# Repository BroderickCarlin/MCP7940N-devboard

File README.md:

# MCP7940N-devboard
A basic devboard for the MCP7940N RTC

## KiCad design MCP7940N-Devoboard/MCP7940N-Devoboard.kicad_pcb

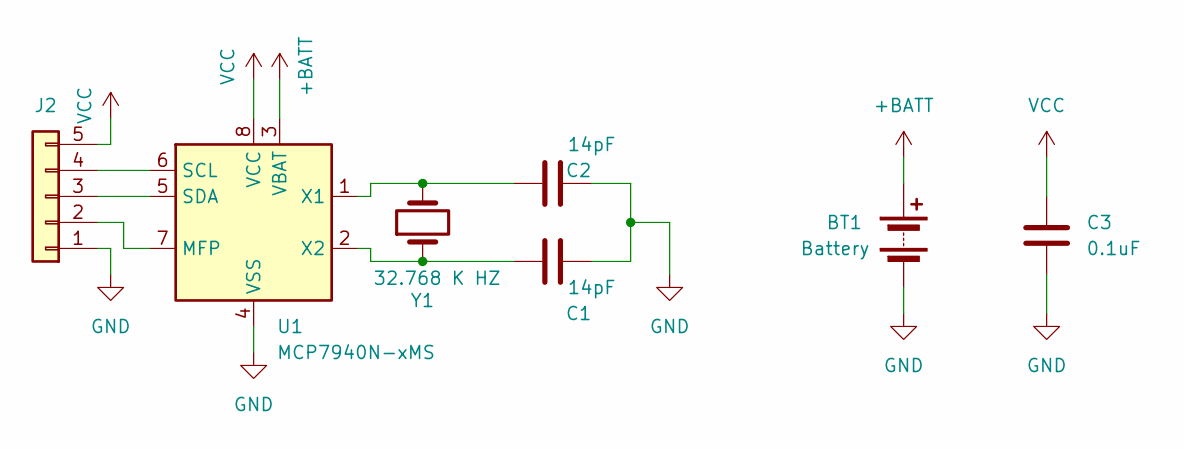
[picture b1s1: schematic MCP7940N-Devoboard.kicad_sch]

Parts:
BT1: Battery; BatteryHolder_Keystone_3034_1x20mm
C1, C2: 14pF; C_0402_1005Metric
C3: 0.1uF; C_0603_1608Metric
J2: Conn_01x05; PinHeader_1x05_P2.54mm_Vertical
U1: MCP7940N-xMS; MSOP-8_3x3mm_P0.65mm
Y1: 32.768 K HZ; Crystal_SMD_SeikoEpson_MA505-2Pin_3.5x1.8mm

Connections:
+BATT: BT1.1 (+), U1.3 (VBAT)
GND: BT1.2 (-), C1.2, C2.2, C3.2, J2.1, U1.4 (VSS)
unnamed: J2.2, U1.7 (MFP)
unnamed: J2.3, U1.5 (SDA)
unnamed: J2.4, U1.6 (SCL)
unnamed: C2.1, U1.1 (X1), Y1.2
unnamed: C1.1, U1.2 (X2), Y1.1
VCC: C3.1, J2.5, U1.8 (VCC)

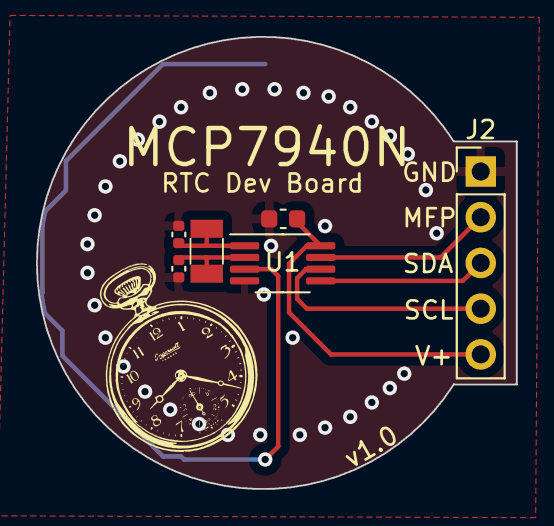
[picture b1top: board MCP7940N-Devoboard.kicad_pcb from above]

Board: 2 copper layers, 26.7 x 25.1 mm, 7 parts (1 on the bottom side), 8 nets.

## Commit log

2023-11-23 feat: Initial commit of dev board
2023-11-23 feat: Add version, text, and graphic
